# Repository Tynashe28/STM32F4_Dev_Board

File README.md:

# STM32F4_Dev_Board

This is a STM32f4 development board designed in Autodesk Eagle. It is Based on the High Perfomance STM32f405RGT6 32-Bit Arm Cortex M4 Microcontroller from ST. 

## Pinout
✔ feature 19 pins broken out from the MCU's Port PB, PA & PC. Refer to the Pcb board for the pinout.

### USB
✔ Support usb full speed @12mbps

### Communication Protocols
✔ For I2C, CAN, SPI and USART connections reference the pins from the datasheet, NOT CHANGED.

## POWER
✔ Can be powered by usd or 12v-24 it can also supply 3.3v and 5v to peripheral connections / devices

## DEBUGING AND UPLOADING FIRMWARE
✔ features a switch to select boot mode (Debug / Run) & Debugging is done via USB. Board doesn't have Serial Wire Debug

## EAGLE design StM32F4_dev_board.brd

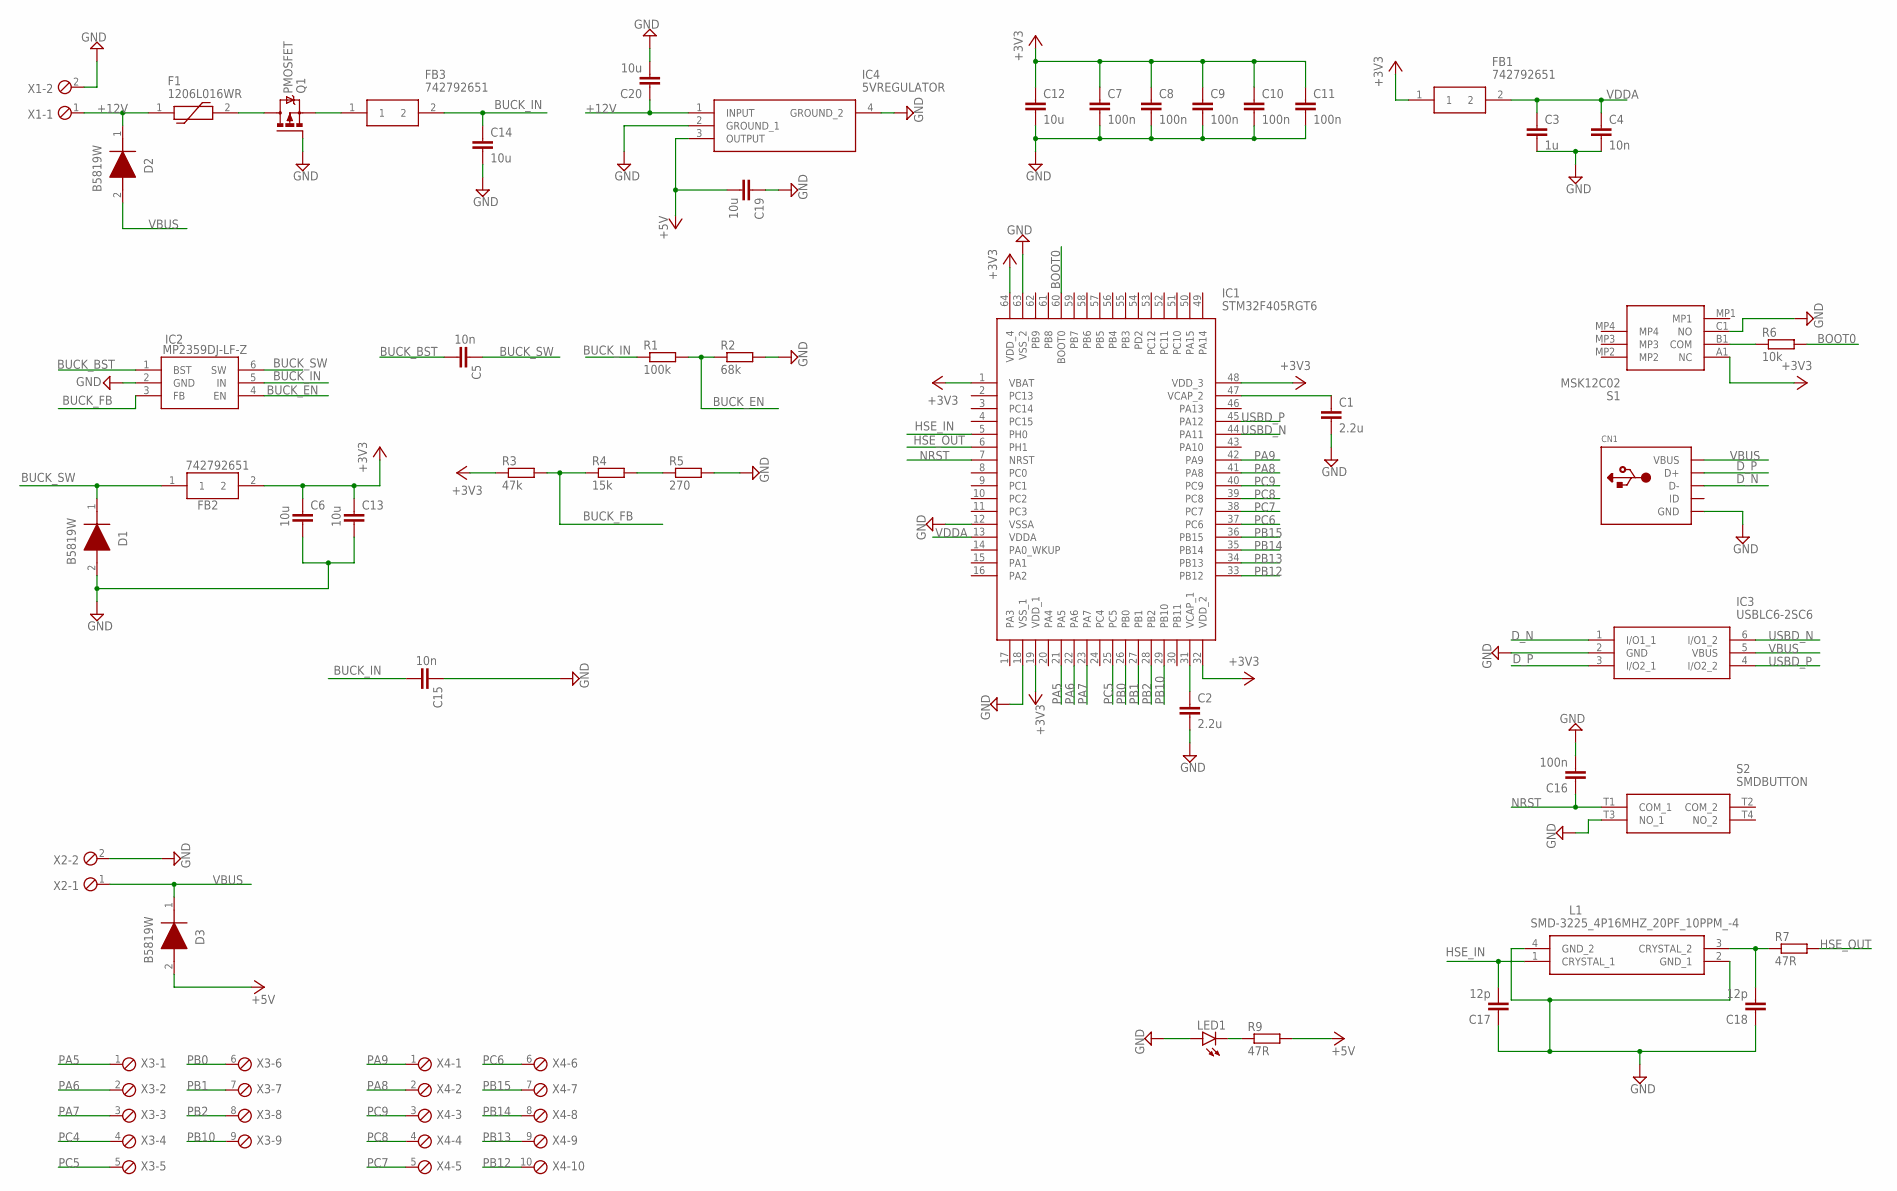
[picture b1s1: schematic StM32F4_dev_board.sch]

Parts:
C1, C2: 2.2u; C0603
C3: 1u; C0805
C4, C5, C15: 10n; C0805
C6, C12, C13, C14, C19, C20: 10u; C0805
C7, C8, C9, C10, C11: 100n; C0805
C16: 100n; C0603K
C17, C18: 12p; C0603K
CN1: USBMINIB; USB-MINIB
D1, D2, D3: B5819W
F1: 1206L016WR; POLYFUSE1206
FB1, FB2, FB3: 742792651; BEADC1608X100N
IC1: STM32F405RGT6; STM32F405RTG6
IC2: MP2359DJ-LF-Z; MP2359
IC3: USBLC6-2SC6; USBLC6
IC4: 5VREGULATOR; SOT23-5V
L1: SMD-3225_4P16MHZ_20PF_10PPM_-4; SMD3225_4P16MHZ20PF10PPM4085
LED1: LEDCHIP-LED0603; CHIP-LED0603
Q1: PMOSFET; SOT23
R1: 100k; R0805
R2: 68k; R0805
R3: 47k; R0805
R4: 15k; R0805
R5: 270; R0805
R6: 10k; R0603
R7, R9: 47R; R0603
S1: MSK12C02
S2: SMDBUTTON
X1, X2: MPT2; 2POL254
X3: MPT9; 9POL254
X4: MPT10; 10POL254

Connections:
+3V3: C6.1, C7.1, C8.1, C9.1, C10.1, C11.1, C12.1, C13.1, FB1.1, FB2.2, IC1.1 (VBAT), IC1.19 (VDD_1), IC1.32 (VDD_2), IC1.48 (VDD_3), IC1.64 (VDD_4), R3.1, S1.A1 (NC)
+5V: C19.2, D3.2 (A), IC4.3 (OUTPUT), R9.2
+12V: C20.1, D2.1 (K), F1.1, IC4.1 (INPUT), X1.1
BOOT0: IC1.60 (BOOT0), R6.2
BUCK_BST: C5.2, IC2.1 (BST)
BUCK_EN: IC2.4 (EN), R1.2, R2.1
BUCK_FB: IC2.3 (FB), R3.2, R4.1
BUCK_IN: C14.1, C15.2, FB3.2, IC2.5 (IN), R1.1
BUCK_SW: C5.1, D1.1 (K), FB2.1, IC2.6 (SW)
D_N: CN1.D-, IC3.1 (I/O1_1)
D_P: CN1.D+, IC3.3 (I/O2_1)
GND: C1.2, C2.2, C3.2, C4.2, C6.2, C7.2, C8.2, C9.2, C10.2, C11.2, C12.2, C13.2, C14.2, C15.1, C16.2, C17.1, C18.1, C19.1, C20.2, CN1.GND, D1.2 (A), IC1.12 (VSSA), IC1.18 (VSS_1), IC1.63 (VSS_2), IC2.2 (GND), IC3.2 (GND), IC4.2 (GROUND_1), IC4.4 (GROUND_2), L1.2 (GND_1), L1.4 (GND_2), LED1.A, Q1.1 (G), R2.2, R5.2, S1.C1 (NO), S2.T3 (NO_1), X1.2, X2.2
HSE_IN: C17.2, IC1.5 (PH0), L1.1 (CRYSTAL_1)
HSE_OUT: IC1.6 (PH1), R7.2
unnamed: C1.1, IC1.47 (VCAP_2)
unnamed: C2.1, IC1.31 (VCAP_1)
unnamed: LED1.C, R9.1
unnamed: R4.2, R5.1
unnamed: F1.2, Q1.3 (D)
unnamed: FB3.1, Q1.2 (S)
unnamed: R6.1, S1.B1 (COM)
unnamed: C18.2, L1.3 (CRYSTAL_2), R7.1
NRST: C16.1, IC1.7 (NRST), S2.T1 (COM_1)
PA5: IC1.21 (PA5), X3.1
PA6: IC1.22 (PA6), X3.2
PA7: IC1.23 (PA7), X3.3
PA8: IC1.41 (PA8), X4.2
PA9: IC1.42 (PA9), X4.1
PB0: IC1.26 (PB0), X3.6
PB1: IC1.27 (PB1), X3.7
PB2: IC1.28 (PB2), X3.8
PB10: IC1.29 (PB10), X3.9
PB12: IC1.33 (PB12), X4.10
PB13: IC1.34 (PB13), X4.9
PB14: IC1.35 (PB14), X4.8
PB15: IC1.36 (PB15), X4.7
PC4: X3.4
PC5: IC1.25 (PC5), X3.5
PC6: IC1.37 (PC6), X4.6
PC7: IC1.38 (PC7), X4.5
PC8: IC1.39 (PC8), X4.4
PC9: IC1.40 (PC9), X4.3
USBD_N: IC1.44 (PA11), IC3.6 (I/O1_2)
USBD_P: IC1.45 (PA12), IC3.4 (I/O2_2)
VBUS: CN1.VBUS, D2.2 (A), D3.1 (K), IC3.5 (VBUS), X2.1
VDDA: C3.1, C4.1, FB1.2, IC1.13 (VDDA)

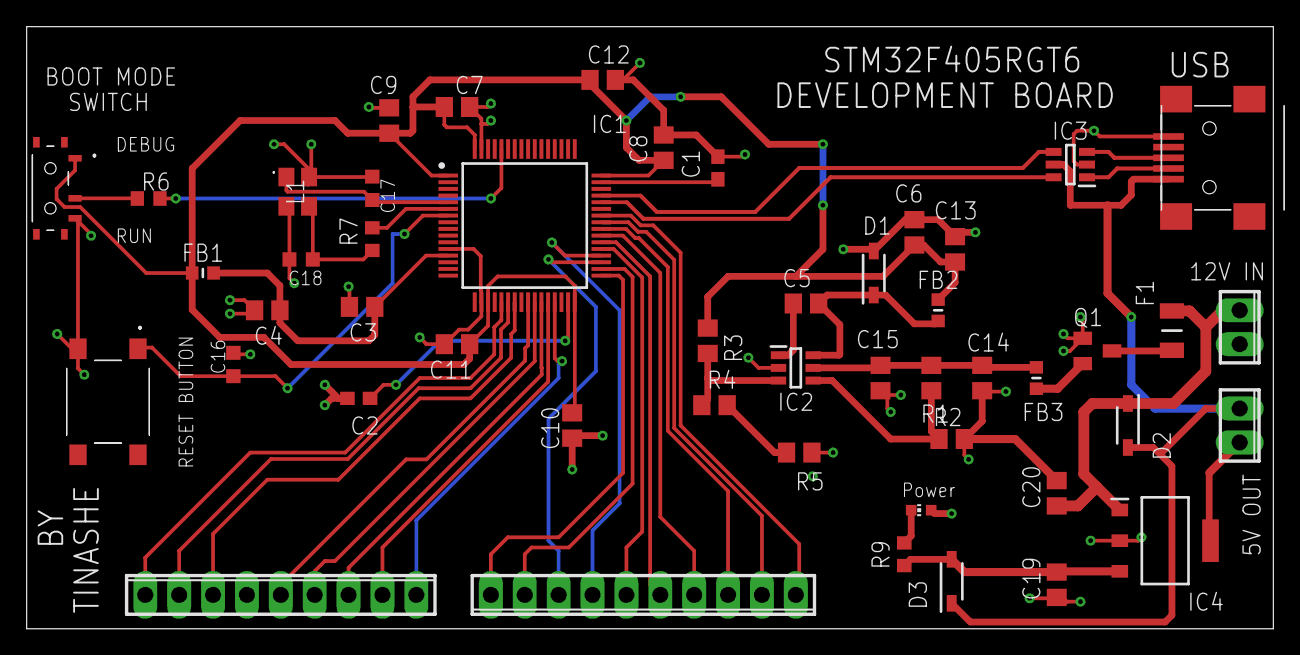
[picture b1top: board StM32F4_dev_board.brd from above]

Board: 2 copper layers, 93.5 x 45.1 mm, 49 parts (0 on the bottom side), 45 nets.

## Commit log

2022-07-19 project init
2022-07-20 routing done
